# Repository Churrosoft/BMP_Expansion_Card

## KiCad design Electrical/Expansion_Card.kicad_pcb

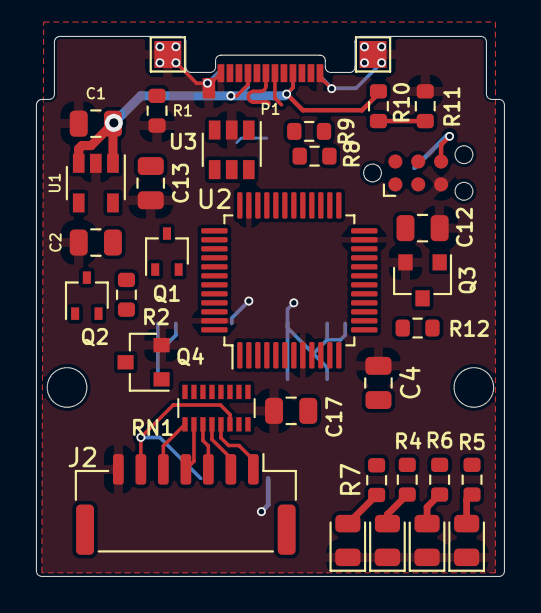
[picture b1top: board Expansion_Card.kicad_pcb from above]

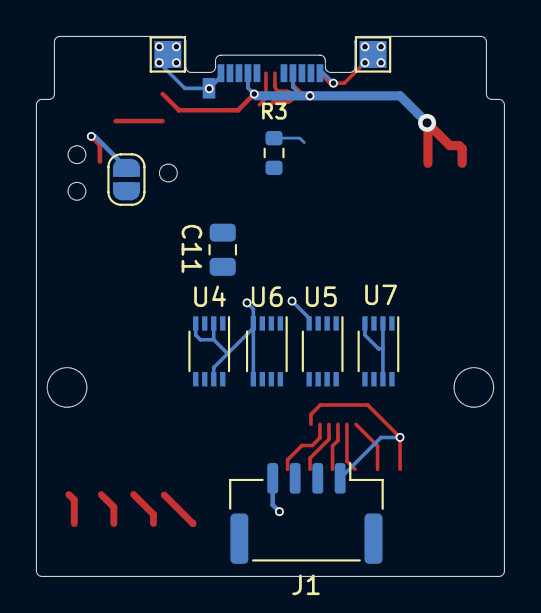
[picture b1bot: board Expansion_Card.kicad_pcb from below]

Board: 4 copper layers, 26.0 x 30.0 mm, 46 parts (10 on the bottom side), 40 nets.

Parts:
C1, C2: 10uF; C_0805_2012Metric
C4, C12, C13, C17: 100nF; C_0805_2012Metric
C11: 4.7uF; C_0805_2012Metric
H1, H2: MountingHole; MountingHole_2.2mm_M2
J1: Serial; JST_GH_BM04B-GHS-TBT_1x04-1MP_P1.25mm_Vertical
J2: Conn_02x05_Counter_Clockwise; JST_GH_BM07B-GHS-TBT_1x07-1MP_P1.25mm_Vertical
J3: Tag connect; Tag-Connect_TC2030-IDC-NL_2x03_P1.27mm_Vertical
JP1: Jumper_NO_Small; SolderJumper-2_P1.3mm_Open_RoundedPad1.0x1.5mm
LED1: GREEN; LED_0805_2012Metric
LED2: RED; LED_0805_2012Metric
LED3: BLUE; LED_0805_2012Metric
LED4: AMBER; LED_0805_2012Metric
P1: USB_C_Plug_USB2.0; USB_C_Plug_Molex_105444
Q1, Q2: CJ3139KW / BSS83P; SOT-323_SC-70
Q3, Q4: BSS123; SOT-23
R1: 5.1k; R_0603_1608Metric
R2, R11, R12: 10k 1% 1/10W; R_0603_1608Metric
R3: 1.5k; R_0603_1608Metric
R4, R5, R6, R7: 4.7k; R_0603_1608Metric
R8, R9: 22R; R_0603_1608Metric
R10: 4.7k 1% 1/10W; R_0603_1608Metric
RN1: R_Pack08; R_Array_Convex_8x0602
TP1, TP2, TP3, TP4: TestPoint; TestPoint_Pad_1.5x1.5mm
U1: AP2112K-3.3; SOT-23-5
U2: STM32F103C8Tx; LQFP-48_7x7mm_P0.5mm
U3: USBLC6-2SC6; SOT-23-6
U4, U5, U6, U7: 74LVC2T45DC; VSSOP-8_2.3x2mm_P0.5mm

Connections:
+3V3: C2.1, C11.1, C12.1, C13.1, J3.1, Q1.3 (D), R4.2, U1.5 (VOUT), U2.1 (VBAT), U2.9 (VDDA), U2.24 (VDD), U2.36 (VDD), U2.48 (VDD), U4.1 (VCCA), U4.5 (DIR), U5.1 (VCCA), U5.5 (DIR), U6.1 (VCCA), U7.1 (VCCA)
/PWR_BR: Q1.1 (G), Q2.1 (G), R2.2
/SYS_SWCLK: J3.4, U2.37 (PA14)
/SYS_SWDIO: J3.2, U2.34 (PA13)
/SYS_SWO: J3.6, JP1.2, U2.43 (PB7)
/TPWR: J1.1, J2.6, Q2.2 (S), RN1.6 (R6.1)
/USB+: R9.2, U2.33 (PA12)
/USB-: R8.2, U2.32 (PA11)
/USBX1+: R3.1, R9.1, U3.4 (I/O2)
/USBX1-: R8.1, U3.6 (I/O1)
/USB_DN: P1.A7 (D-), U3.1 (I/O1)
/USB_DP: P1.A6 (D+), U3.3 (I/O2)
/_VBUS: R10.2, R11.1
/iTDO: JP1.1, U6.2 (1A)
/xRST: Q4.1 (G), RN1.12 (R5.2)
/xRXD: RN1.10 (R7.2), U6.6 (2B)
/xTCK: RN1.15 (R2.2), U5.7 (1B)
/xTDI: RN1.13 (R4.2), U5.6 (2B)
/xTDO: RN1.14 (R3.2), U6.7 (1B)
/xTMS: RN1.16 (R1.2), U7.6 (2B)
/xTPWR: C4.1, R12.1, RN1.11 (R6.2), U4.8 (VCCB), U5.8 (VCCB), U6.8 (VCCB), U7.8 (VCCB)
/xTXD: RN1.9 (R8.2), U4.6 (2B)
GND: C1.2, C2.2, C4.2, C11.2, C12.2, C13.2, C17.1, J1.4, J2.7, J3.5, LED1.1 (K), LED2.1 (K), LED3.1 (K), LED4.1 (K), P1.A1 (GND), P1.A12 (GND), P1.B1 (GND), P1.B12 (GND), P1.S1 (SHIELD), Q3.2 (S), Q4.2 (S), R1.2, R11.2, TP1.1, TP2.1, TP3.1, TP4.1, U1.2 (GND), U2.8 (VSSA), U2.23 (VSS), U2.35 (VSS), U2.47 (VSS), U3.2 (GND), U4.2 (1A), U4.4 (GND), U4.7 (1B), U5.4 (GND), U6.4 (GND), U6.5 (DIR), U7.2 (1A), U7.4 (GND), U7.7 (1B)
unnamed: LED1.2 (A), R4.1
unnamed: LED2.2 (A), R5.1
unnamed: LED3.2 (A), R6.1
unnamed: LED4.2 (A), R7.1
unnamed: P1.A5 (CC), R1.1
unnamed: Q1.2 (S), Q2.3 (D), R2.1
unnamed: Q3.3 (D), R12.2
unnamed: J2.5, RN1.1 (R1.1)
unnamed: J2.4, RN1.2 (R2.1)
unnamed: J2.3, RN1.3 (R3.1)
unnamed: J2.2, RN1.4 (R4.1)
unnamed: J2.1, RN1.5 (R5.1)
unnamed: J1.3, RN1.7 (R7.1)
unnamed: J1.2, RN1.8 (R8.1)
unnamed: C17.2, U2.7 (NRST)
unnamed: R3.2, U2.29 (PA8)
VBUS: C1.1, P1.A4 (VBUS), P1.A9 (VBUS), P1.B4 (VBUS), P1.B9 (VBUS), R10.1, U1.1 (VIN), U1.3 (EN)

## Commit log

2021-09-17 init

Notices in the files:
Electrical/Expansion_Card.kicad_pcb:
This work is licensed under a Creative Commons Attribution 4.0 International License
